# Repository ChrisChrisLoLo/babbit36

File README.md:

# babbit36

![image of babbit36](https://lh3.googleusercontent.com/pw/AMWts8DwCoTWacwhSSqrcxAkfQMXyfk-6-LHsO64JU0l3AVrd6OUB-6Lfk-UIZn23yizijxunzSFsNKgVUzwrF0GgiBsBwEAGf0NMvLM-saS2Y9kz2beIGW-XCEwR5fnhEvlPQb0Ye-_y-kxsEA9hRosB1_8=w1896-h1068-no?authuser=0
)

A 36 key low profile wireless ortholinear board. Uses a Seediuno XIAO as the MCU, and runs on ZMK.
Featues:
  - Low Profile, uses CFX keycaps
  - Commodity parts, only non standard part is the shift register
  - Relatively affordable! 
    - Case only requires one CNC/3D Printed part and one FR4 backplate

## Note
This keyboard uses CFX spacing, and therefore requires Chosfox CFX keycaps, or keycaps with similar spacing.

## Status
v0 is functional and works as is!  

## PCB/CNC case

You can generate the gerbers from source in the pcb directory, and send off imediately to PCBWay or the like. There's one gerber for the keyboard and another gerber for the backplate of the case. There's also step files ready to use to order your own 3DP/CNC case. My CNC case was sponsored by PCBWay. I was a bit anxious about my CNC file since this is my most complicated keyboard case to date, but PCBWay did a fantastic job! I was very happy that the tolerances were good, that the finishing looked great, and that it was all at a great price given the complexity of the case! I highly recommend their services for CNC prototyping/manufacturing!

## BOM
The following is the materials you will want/need to make your own babbit36. Note that anything amount after a + denotes the rough amount of spares you may want to have when ordering the parts.
| Part | Count | Notes |
|------|---------------|----------|
| PCB | 1 |  |
|Kailh Choc Hotswap Switches |36+4|| 	
|LL4148 SMD Diodes |	36+4 |	This board uses SMD diodes exclusively. I found though-hole diodes often easily slipped around in a way such that the board was no longer able to fit inside the case|
|Seeduino XIAO nrf52|1||
|74hc595 SMD|1|SMD Shift Register|
|SMD power switch|1||
|Lipo battery|1|A 3.7V 110mAh 301230 will fit nicely in the case|
|Rubber Feet 	|6+2| 	Any should generally work, though I'm using ~2.5mm thick ones, as they give more space for screw heads, as well as the magnetic connector I'm using|
|CNC Printed Case 	|1 	|You could use PCB printing services like PCBWay to make one in resin, though I haven't confirmed if they'd be durable enough to survive in transit|
|PCB/FR4 backplate | 1| For the back of the keyboard case. Can be found in the pcb folder |
|M2 4mm Screw |	6+2 |	Screws for the PCB and case. Be careful of the size of the screw head! the flatter the better!

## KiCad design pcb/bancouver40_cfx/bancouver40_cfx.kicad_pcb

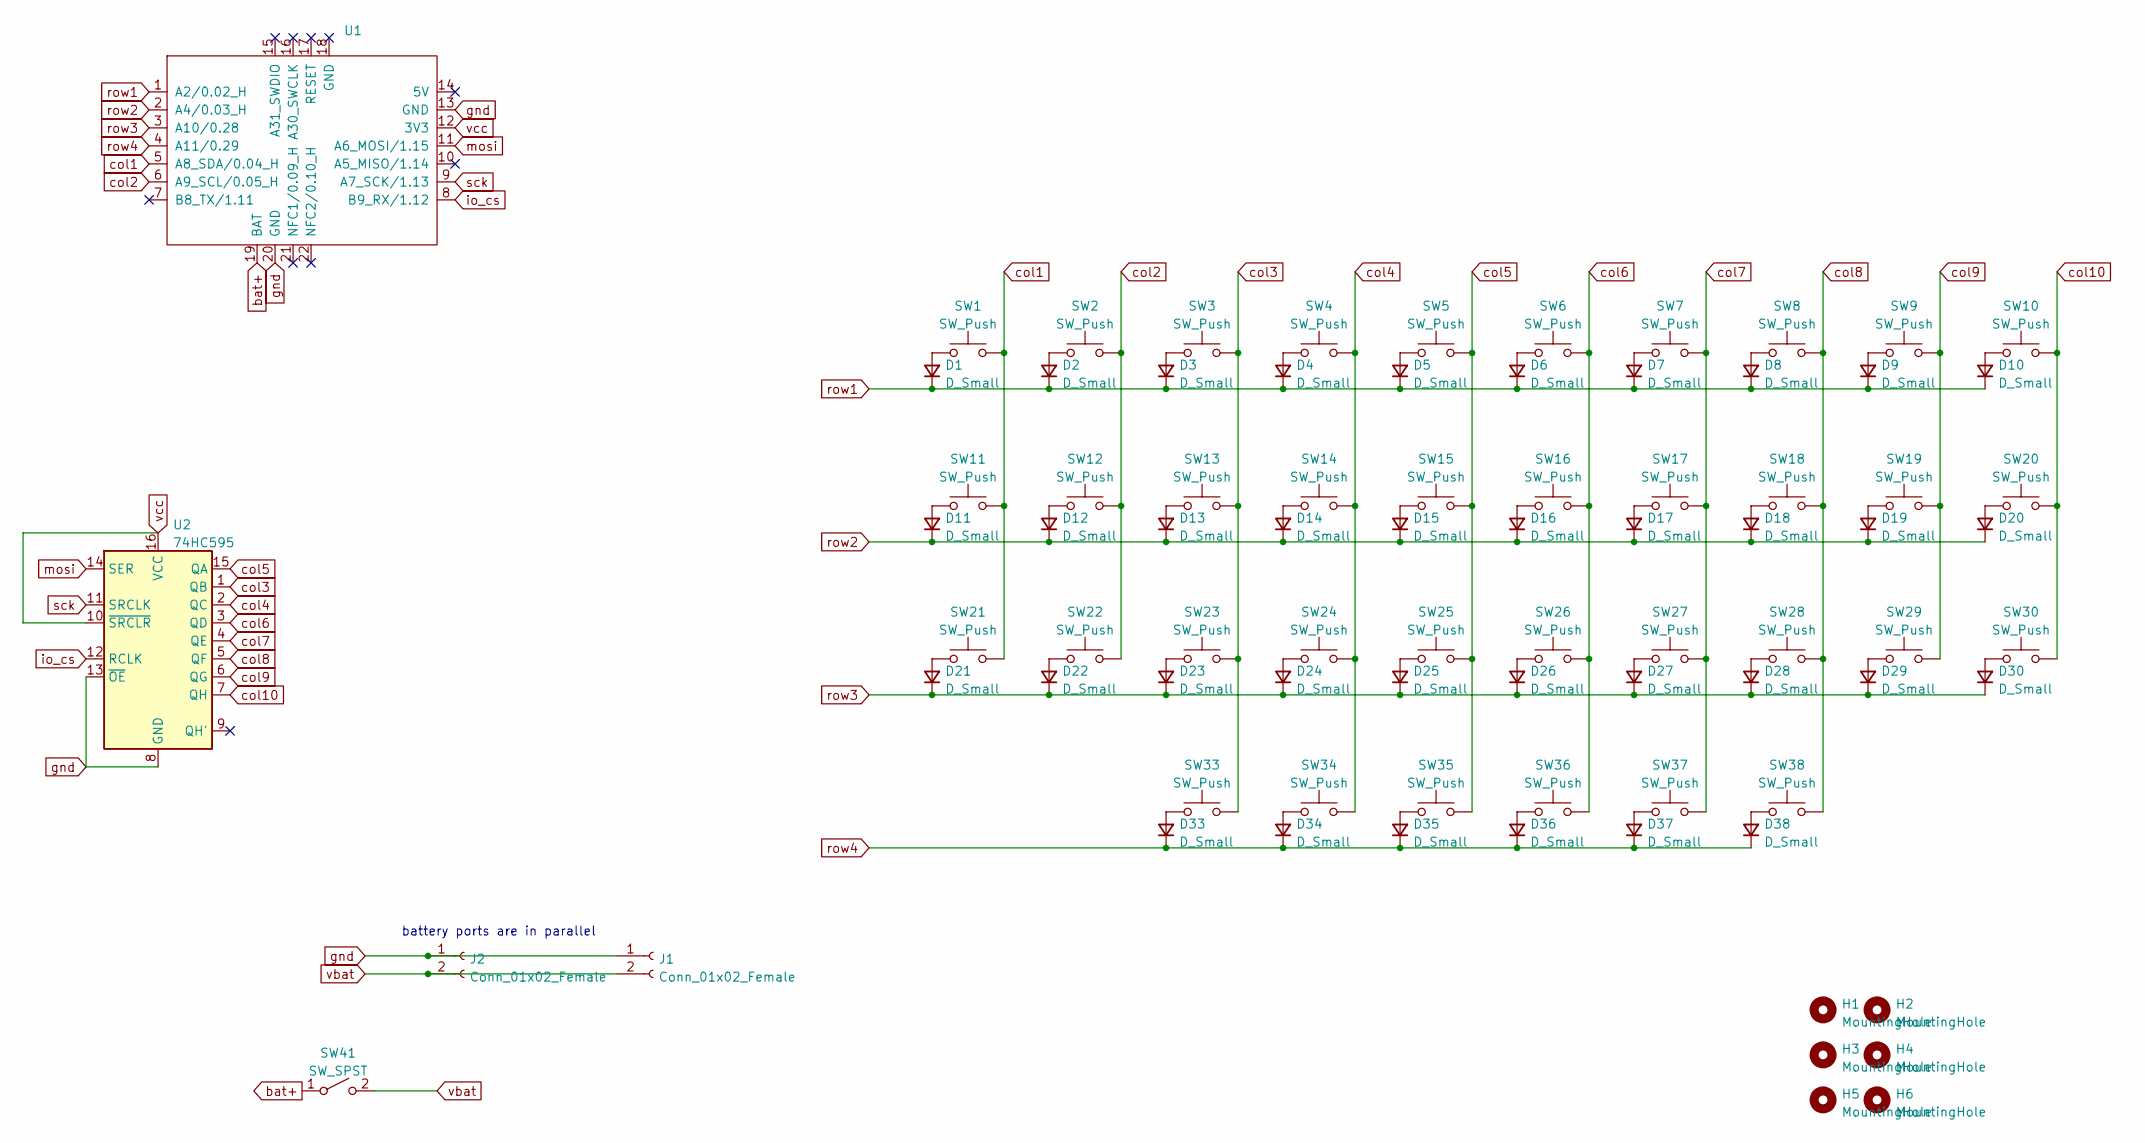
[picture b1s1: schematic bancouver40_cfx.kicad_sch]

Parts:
D1, D2, D3, D4, D5, D6, D7, D8, D9, D10, D11, D12, D13, D14, D15, D16, D17, D18, D19, D20, D21, D22, D23, D24, D25, D26, D27, D28, D29, D30, D33, D34, D35, D36, D37, D38: D_Small
H1, H2, H3, H4, H5, H6: MountingHole
J1: Conn_01x02_Female; JST_PH_S2B-PH-K_1x02_P2.00mm_Horizontal
J2: Conn_01x02_Female; PinHeader_1x02_P2.54mm_Vertical
SW1, SW2, SW3, SW4, SW5, SW6, SW7, SW8, SW9, SW10, SW11, SW12, SW13, SW14, SW15, SW16, SW17, SW18, SW19, SW20, SW21, SW22, SW23, SW24, SW25, SW26, SW27, SW28, SW29, SW30, SW33, SW34, SW35, SW36, SW37, SW38: SW_Push; Kailh_socket_PG1350
SW41: SW_SPST; SW_SPDT_PCM12
U1: (no value)
U2: 74HC595; SOIC-16_3.9x9.9mm_P1.27mm

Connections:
unnamed: D1.2 (A), SW1.1
unnamed: D2.2 (A), SW2.1
unnamed: D3.2 (A), SW3.1
unnamed: D4.2 (A), SW4.1
unnamed: D5.2 (A), SW5.1
unnamed: D6.2 (A), SW6.1
unnamed: D7.2 (A), SW7.1
unnamed: D8.2 (A), SW8.1
unnamed: D9.2 (A), SW9.1
unnamed: D10.2 (A), SW10.1
unnamed: D11.2 (A), SW11.1
unnamed: D12.2 (A), SW12.1
unnamed: D13.2 (A), SW13.1
unnamed: D14.2 (A), SW14.1
unnamed: D15.2 (A), SW15.1
unnamed: D16.2 (A), SW16.1
unnamed: D17.2 (A), SW17.1
unnamed: D18.2 (A), SW18.1
unnamed: D19.2 (A), SW19.1
unnamed: D20.2 (A), SW20.1
unnamed: D21.2 (A), SW21.1
unnamed: D22.2 (A), SW22.1
unnamed: D23.2 (A), SW23.1
unnamed: D24.2 (A), SW24.1
unnamed: D25.2 (A), SW25.1
unnamed: D26.2 (A), SW26.1
unnamed: D27.2 (A), SW27.1
unnamed: D28.2 (A), SW28.1
unnamed: D29.2 (A), SW29.1
unnamed: D30.2 (A), SW30.1
unnamed: D33.2 (A), SW33.1
unnamed: D34.2 (A), SW34.1
unnamed: D35.2 (A), SW35.1
unnamed: D36.2 (A), SW36.1
unnamed: D37.2 (A), SW37.1
unnamed: D38.2 (A), SW38.1
bat+: SW41.1 (A), U1.19 (BAT)
col1: SW1.2, SW11.2, SW21.2, U1.5 (A8_SDA/0.04_H)
col2: SW2.2, SW12.2, SW22.2, U1.6 (A9_SCL/0.05_H)
col3: SW3.2, SW13.2, SW23.2, SW33.2, U2.1 (QB)
col4: SW4.2, SW14.2, SW24.2, SW34.2, U2.2 (QC)
col5: SW5.2, SW15.2, SW25.2, SW35.2, U2.15 (QA)
col6: SW6.2, SW16.2, SW26.2, SW36.2, U2.3 (QD)
col7: SW7.2, SW17.2, SW27.2, SW37.2, U2.4 (QE)
col8: SW8.2, SW18.2, SW28.2, SW38.2, U2.5 (QF)
col9: SW9.2, SW19.2, SW29.2, U2.6 (QG)
col10: SW10.2, SW20.2, SW30.2, U2.7 (QH)
gnd: J1.1, J2.1, U1.13 (GND), U1.20 (GND), U2.8 (GND), U2.13 (~OE)
io_cs: U1.8 (B9_RX/1.12), U2.12 (RCLK)
mosi: U1.11 (A6_MOSI/1.15), U2.14 (SER)
reset: U1.17 (RESET)
row1: D1.1 (K), D2.1 (K), D3.1 (K), D4.1 (K), D5.1 (K), D6.1 (K), D7.1 (K), D8.1 (K), D9.1 (K), D10.1 (K), U1.1 (A2/0.02_H)
row2: D11.1 (K), D12.1 (K), D13.1 (K), D14.1 (K), D15.1 (K), D16.1 (K), D17.1 (K), D18.1 (K), D19.1 (K), D20.1 (K), U1.2 (A4/0.03_H)
row3: D21.1 (K), D22.1 (K), D23.1 (K), D24.1 (K), D25.1 (K), D26.1 (K), D27.1 (K), D28.1 (K), D29.1 (K), D30.1 (K), U1.3 (A10/0.28)
row4: D33.1 (K), D34.1 (K), D35.1 (K), D36.1 (K), D37.1 (K), D38.1 (K), U1.4 (A11/0.29)
sck: U1.9 (A7_SCK/1.13), U2.11 (SRCLK)
vbat: J1.2, J2.2, SW41.2 (B)
vcc: U1.12 (3V3), U2.10 (~SRCLR), U2.16 (VCC)

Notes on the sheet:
battery ports are in parallel

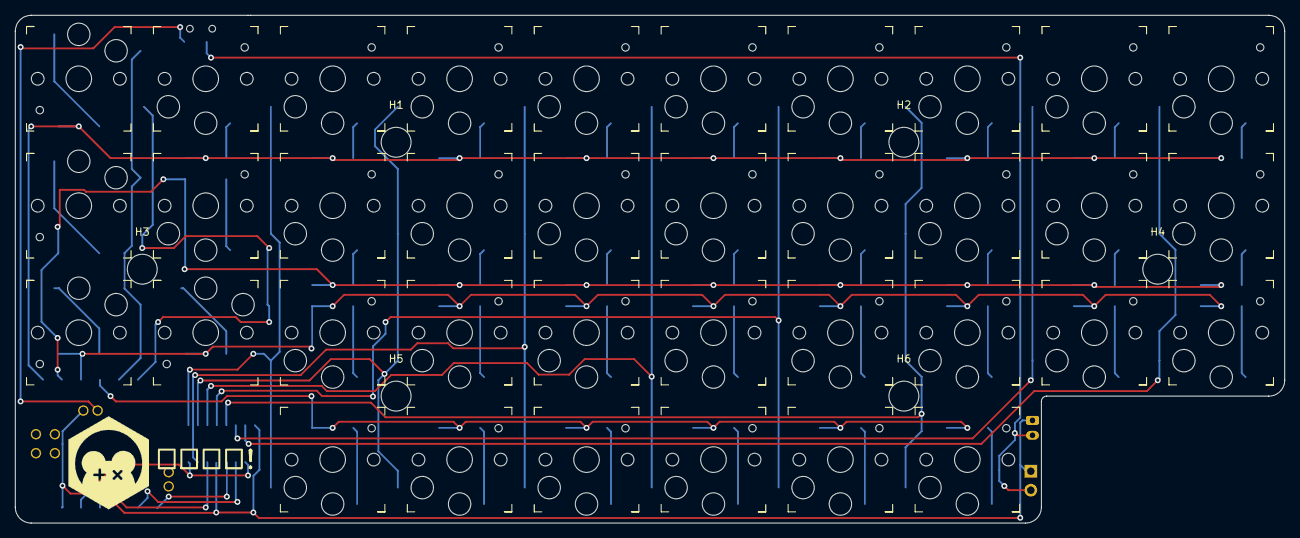
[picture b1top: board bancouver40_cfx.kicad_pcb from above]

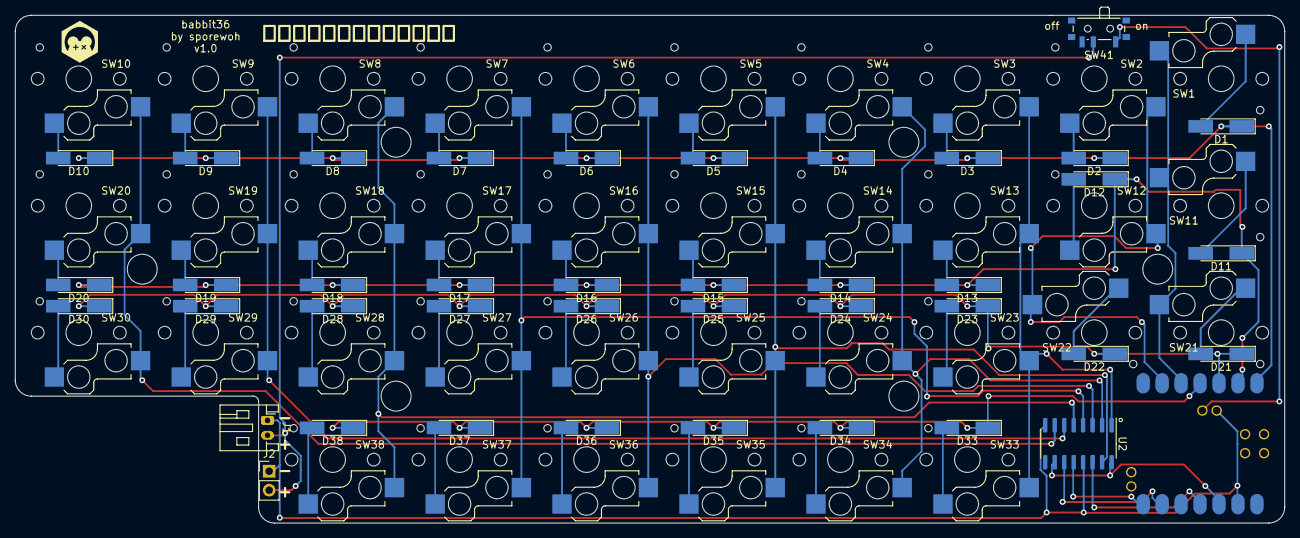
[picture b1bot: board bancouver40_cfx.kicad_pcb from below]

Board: 2 copper layers, 170.0 x 68.0 mm, 83 parts (41 on the bottom side), 57 nets.

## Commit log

2022-12-23 init
2023-01-21 add case
2023-11-27 add cnc files
